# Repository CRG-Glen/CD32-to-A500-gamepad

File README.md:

# CD32 to The A500 Gamepad

This is a replacement PCB for The A500 gamepad making it a true CD32 pad.

Based on Commodore CD32 gamepad schematics.

YouTube video on the design, assembly and testing of this project can be viewed here - https://youtu.be/vLGpuEnnuxA

## Assembly

Within the JLCPCB folder you will find Gerbers along with a BOM and CPL files suited to LSSC components.

I recommend having the board produced with the EINT finish and get JLC (or equal) to do all SMD work as its 0402 and very fiddly.

You must fit the through hole capacitor yourself (47uF 2mm pin spacing 5mm diameter) as it needs to be folded over onto the PCB.

For the shoulder button switches, you can just take them off the original PCB or the part numbers are below.

You will obviously need a new wire, I'd recommend a simple DB9 extension cable and cut the end off.  The holes labelled 1-9
on the PCB correspond to pins 1-9  on the DB9.  This is at 1.27mm pitch so be careful not to bridge anything!

## Bill of Materials

| Designation | Value | Type |
| --- | --- | --- |
| U1 | 74LS165 | SOIC16 |
| U2 | 74LS125 | SOIC14 |
| R1 | 220ohm 1% | 0402 |
| R10 | 1k ohm 1% | 0402 |
| R11 | 10k ohm 1% | 0402 |
| R15 | 100ohm 1% | 0402 |
| RP1 | 10k 1% | 4x0402 |
| RP2 | 10k 1% | 4x0402 |
| C1 | 100pF | 0402 ceramic |
| C2 | 47uF | 2mm lead spacing 5mm diameter *remember to fold this over* |
| C3 | 1000pF | 0402 ceramic |
| C4 | 0.1uF | 0402 ceramic |
| C5 | 0.1uF | 0402 ceramic |
| FB1 | 1kohm @ 100MHz | 0402 |
| SW9 | PTS645Vx39-2LFS | Tactile SPST Angled Switch *or take this off the old PCB* |
| SW10 | PTS645Vx39-2LFS | Tactile SPST Angled Switch *or take this off the old PCB* |

## License

CERN Open Hardware Licence v2

Do with as you like just don't blame me if your Amiga goes up in smoke!

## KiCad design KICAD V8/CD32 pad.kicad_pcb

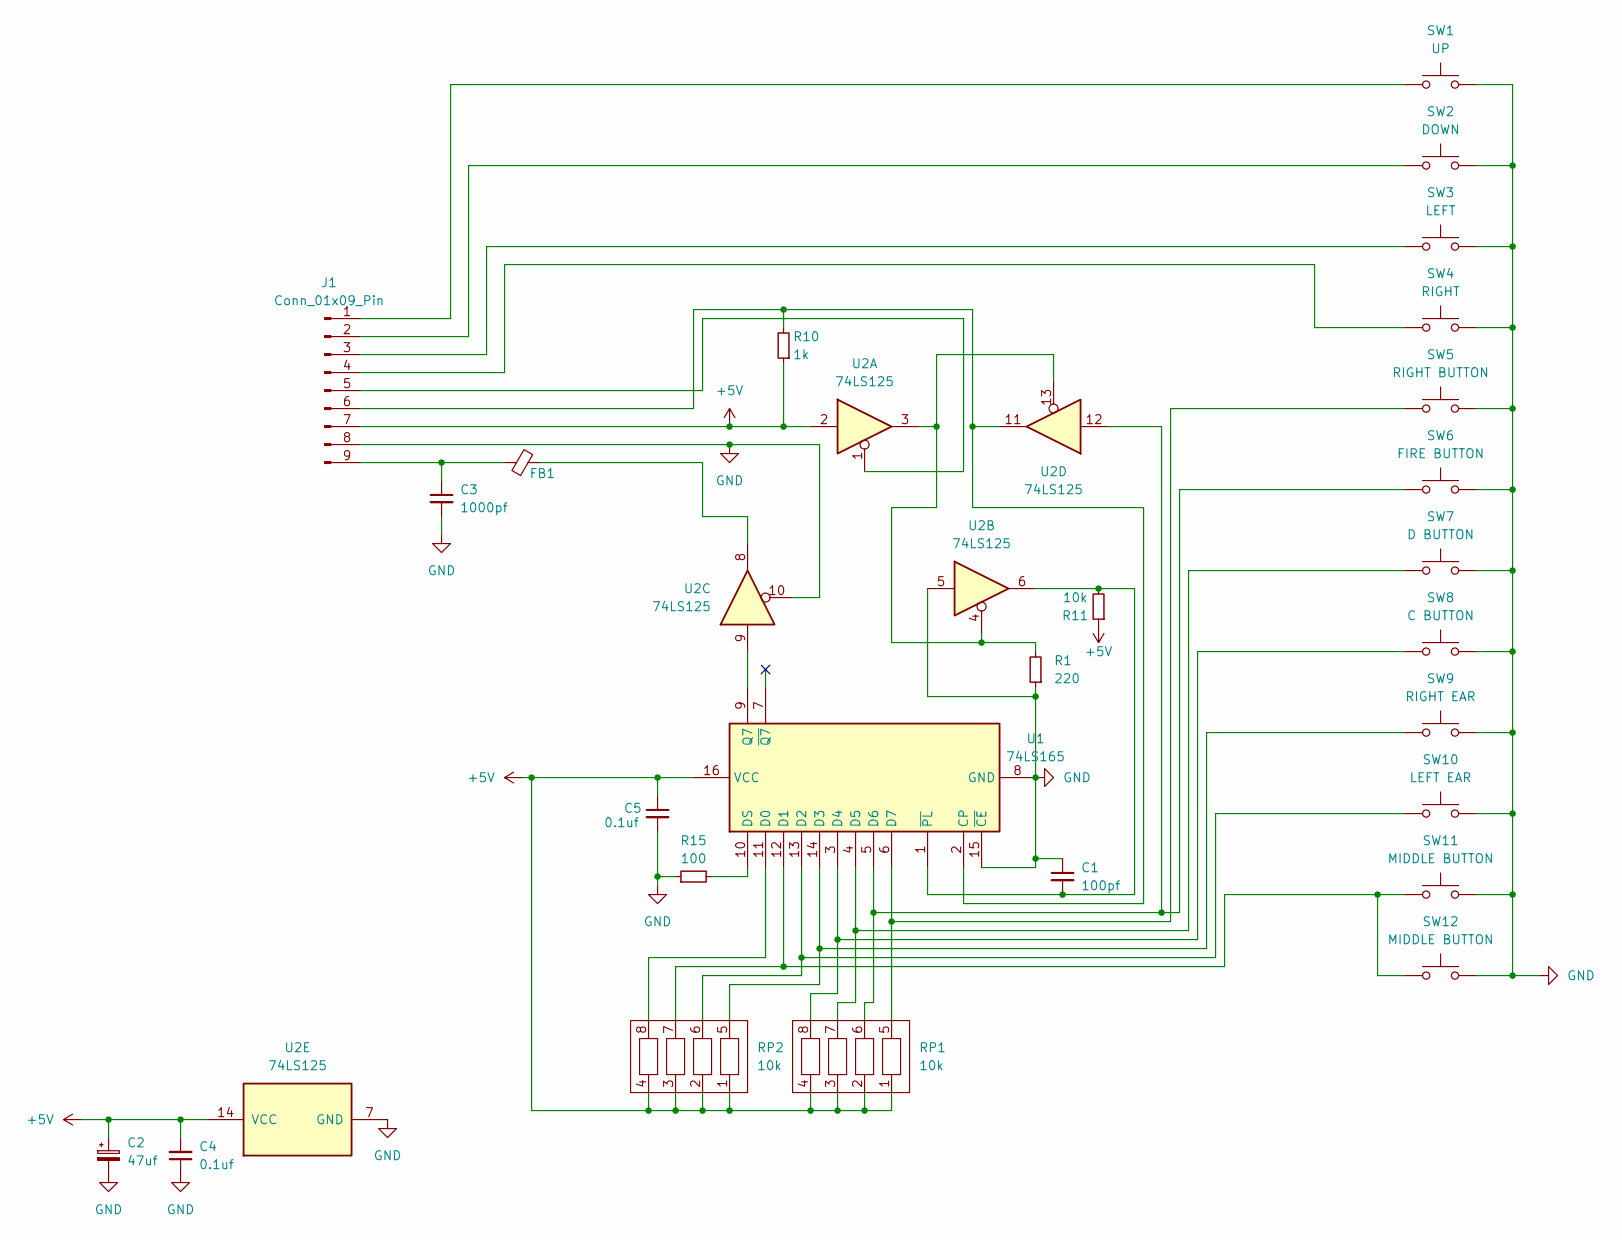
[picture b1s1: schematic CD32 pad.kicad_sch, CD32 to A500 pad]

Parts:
C1: 100pf; C_0402_1005Metric_Pad0.74x0.62mm_HandSolder; LCSC C1546
C2: 47uf; CP_Radial_D5.0mm_P2.00mm
C3: 1000pf; C_0402_1005Metric_Pad0.74x0.62mm_HandSolder; LCSC C1523
C4, C5: 0.1uf; C_0402_1005Metric_Pad0.74x0.62mm_HandSolder; LCSC C307331
FB1: FerriteBead_Small; C_0402_1005Metric_Pad0.74x0.62mm_HandSolder; LCSC C32472
J1: Conn_01x09_Pin; PinHeader_1x09_P1.27mm_Vertical
R1: 220; R_0402_1005Metric_Pad0.72x0.64mm_HandSolder; LCSC C25091
R10: 1k; R_0402_1005Metric_Pad0.72x0.64mm_HandSolder; LCSC C11702
R11: 10k; R_0402_1005Metric_Pad0.72x0.64mm_HandSolder; LCSC C25744
R15: 100; R_0402_1005Metric_Pad0.72x0.64mm_HandSolder; LCSC C25076
RP1, RP2: 10k; R_Array_Concave_4x0402; LCSC C414600
SW1: UP; Button contact 8mm
SW2: DOWN; Button contact 8mm
SW3: LEFT; Button contact 8mm
SW4: RIGHT; Button contact 8mm
SW5: RIGHT BUTTON; Button contact 8mm
SW6: FIRE BUTTON; Button contact 8mm
SW7: D BUTTON; Button contact 8mm
SW8: C BUTTON; Button contact 8mm
SW9: RIGHT EAR; SW_Tactile_SPST_Angled_PTS645Vx39-2LFS; LCSC C221887
SW10: LEFT EAR; SW_Tactile_SPST_Angled_PTS645Vx39-2LFS; LCSC C221887
SW11, SW12: MIDDLE BUTTON; Button contact 8mm
U1: 74LS165; SOIC-16_3.9x9.9mm_P1.27mm; LCSC C7742
U2: 74LS125; SOIC-14_3.9x8.7mm_P1.27mm; LCSC C7734

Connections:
+5V: C2.1, C4.2, C5.1, J1.7, R10.1, R11.1, RP1.1, RP1.2, RP1.3, RP1.4, RP2.1, RP2.2, RP2.3, RP2.4, U1.16 (VCC), U2.2, U2.14 (VCC)
GND: C1.1, C2.2, C3.2, C4.1, C5.2, J1.8, R1.1, R15.1, SW1.2, SW2.2, SW3.2, SW4.2, SW5.2, SW6.2, SW7.2, SW8.2, SW9.2, SW10.2, SW11.2, SW12.2, U1.8 (GND), U1.15 (~CE), U2.5, U2.7 (GND), U2.10
unnamed: FB1.2, U2.8
unnamed: J1.1, SW1.1
unnamed: J1.2, SW2.1
unnamed: J1.3, SW3.1
unnamed: J1.4, SW4.1
unnamed: J1.5, U2.1
unnamed: J1.6, R10.2, U1.2 (CP), U2.11
unnamed: C3.1, FB1.1, J1.9
unnamed: R1.2, U2.3, U2.4, U2.13
unnamed: RP2.8, U1.11 (D0)
unnamed: RP2.7, SW11.1, SW12.1, U1.12 (D1)
unnamed: RP2.6, SW10.1, U1.13 (D2)
unnamed: RP2.5, SW9.1, U1.14 (D3)
unnamed: RP1.8, SW8.1, U1.3 (D4)
unnamed: RP1.7, SW7.1, U1.4 (D5)
unnamed: RP1.6, SW6.1, U1.5 (D6), U2.12
unnamed: RP1.5, SW5.1, U1.6 (D7)
unnamed: R15.2, U1.10 (DS)
unnamed: U1.9 (Q7), U2.9
unnamed: C1.2, R11.2, U1.1 (~PL), U2.6

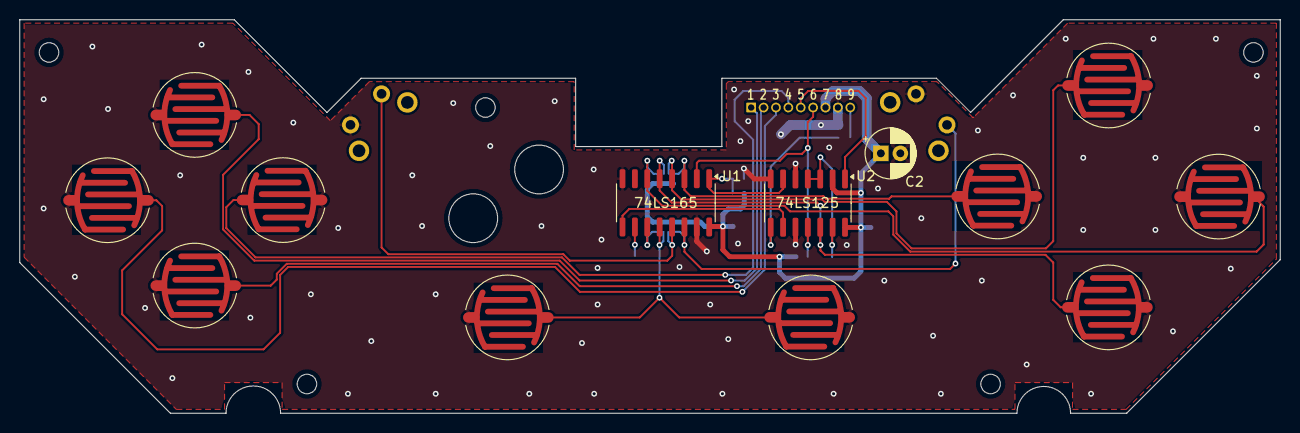
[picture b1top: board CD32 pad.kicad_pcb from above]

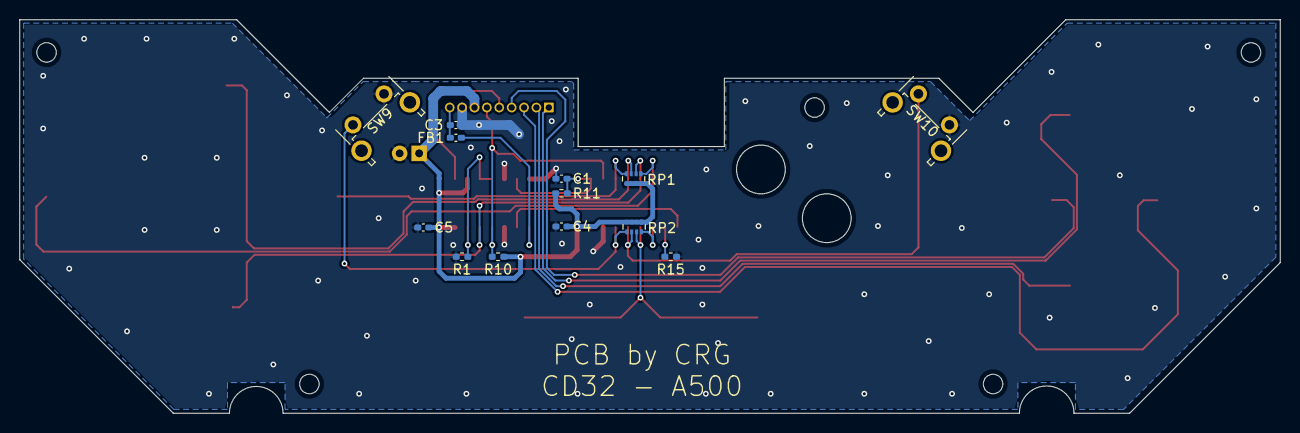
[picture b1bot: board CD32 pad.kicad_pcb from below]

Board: 2 copper layers, 129.3 x 40.3 mm, 27 parts (13 on the bottom side), 22 nets.

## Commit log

2026-02-16 Released 16-02-26
2026-02-16 Rename Board 3D.png to Board3D.png
2026-02-19 BOM revised in readme
